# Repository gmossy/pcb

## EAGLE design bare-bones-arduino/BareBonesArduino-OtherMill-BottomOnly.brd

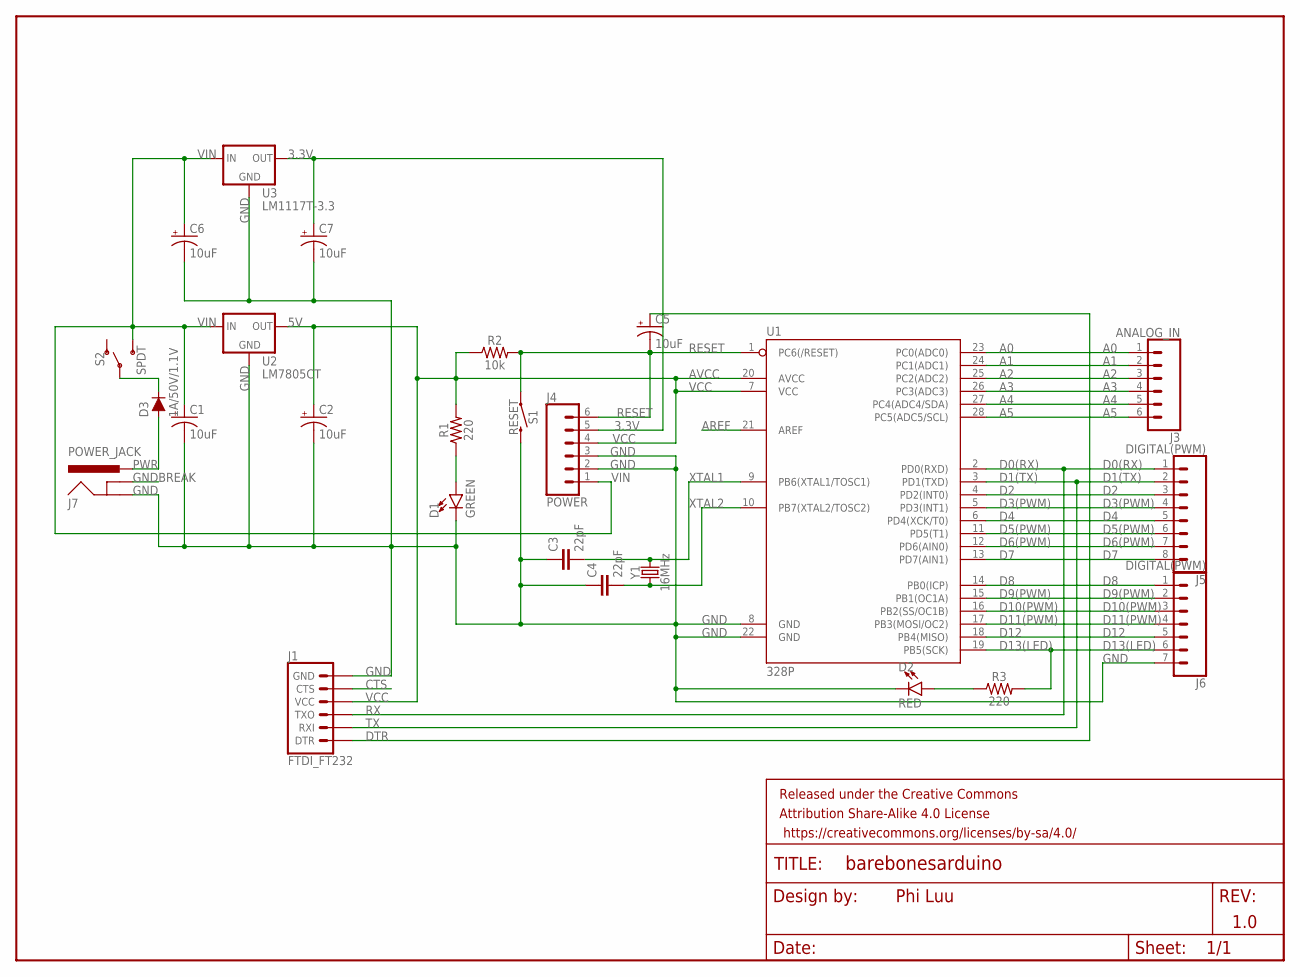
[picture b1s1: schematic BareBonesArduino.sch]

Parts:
C1, C2, C5, C6, C7: 10uF; CPOL-RADIAL-2.5MM-5MM
C3, C4: 22pF; CAP-PTH-2.54
D1: GREEN; LED_5MM
D2: RED; LED_5MM
D3: 1A/50V/1.1V; DIODE-1N4001
FRAME1: FRAME-LETTER; CREATIVE_COMMONS
J1: FTDI_FT232; 1X06
J3: ANALOG_IN; 1X06
J4: POWER; 1X06
J5: DIGITAL(PWM); 1X08
J6: DIGITAL(PWM); 1X07
J7: POWER_JACK; POWER_JACK_PTH
R1, R3: 220; AXIAL-0.3
R2: 10k; AXIAL-0.3
S1: RESET; TACTILE_SWITCH_PTH_6.0MM
S2: SPDT; SWITCH_SPDT_PTH_11.6X4.0MM
U1: 328P; DIP28
U2: LM7805CT; TO-220-ALT
U3: LM1117T-3.3; 78XXL
Y1: 16MHz; HC49US

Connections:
3.3V: C7.1 (+), J4.5, U3.GND (OUT)
A0: J3.1, U1.23 (PC0(ADC0))
A1: J3.2, U1.24 (PC1(ADC1))
A2: J3.3, U1.25 (PC2(ADC2))
A3: J3.4, U1.26 (PC3(ADC3))
A4: J3.5, U1.27 (PC4(ADC4/SDA))
A5: J3.6, U1.28 (PC5(ADC5/SCL))
AREF: U1.21 (AREF)
CTS: J1.5 (CTS)
D0(RX): J1.3 (TXO), J5.1, U1.2 (PD0(RXD))
D1(TX): J1.2 (RXI), J5.2, U1.3 (PD1(TXD))
D2: J5.3, U1.4 (PD2(INT0))
D3(PWM): J5.4, U1.5 (PD3(INT1))
D4: J5.5, U1.6 (PD4(XCK/T0))
D5(PWM): J5.6, U1.11 (PD5(T1))
D6(PWM): J5.7, U1.12 (PD6(AIN0))
D7: J5.8, U1.13 (PD7(AIN1))
D8: J6.1, U1.14 (PB0(ICP))
D9(PWM): J6.2, U1.15 (PB1(OC1A))
D10(PWM): J6.3, U1.16 (PB2(SS/OC1B))
D11(PWM): J6.4, U1.17 (PB3(MOSI/OC2))
D12: J6.5, U1.18 (PB4(MISO))
D13(LED): J6.6, R3.P$2 (2), U1.19 (PB5(SCK))
DTR: C5.1 (+), J1.1 (DTR)
GND: C1.2 (-), C2.2 (-), C3.1, C4.1, C6.2 (-), C7.2 (-), D1.K (C), D2.K (C), J1.6 (GND), J4.2, J4.3, J6.7, J7.GND, S1.3 (2), U1.8 (GND), U1.22 (GND), U2.GND, U3.IN (GND)
GNDBREAK: J7.GNDBREAK
unnamed: D2.A, R3.P$1 (1)
unnamed: D3.C, S2.2
unnamed: D1.A, R1.P$1 (1)
PWR: D3.A, J7.PWR
RESET: C5.2 (-), J4.6, R2.P$2 (2), S1.1, U1.1 (PC6(/RESET))
VCC: C2.1 (+), J1.4 (VCC), J4.4, R1.P$2 (2), R2.P$1 (1), U1.7 (VCC), U1.20 (AVCC), U2.OUT
VIN: C1.1 (+), C6.1 (+), J4.1, S2.3 (S), U2.IN, U3.OUT (IN)
XTAL1: C3.2, U1.9 (PB6(XTAL1/TOSC1)), Y1.2
XTAL2: C4.2, U1.10 (PB7(XTAL2/TOSC2)), Y1.1

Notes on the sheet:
Phi Luu
1.0
AVCC
GND

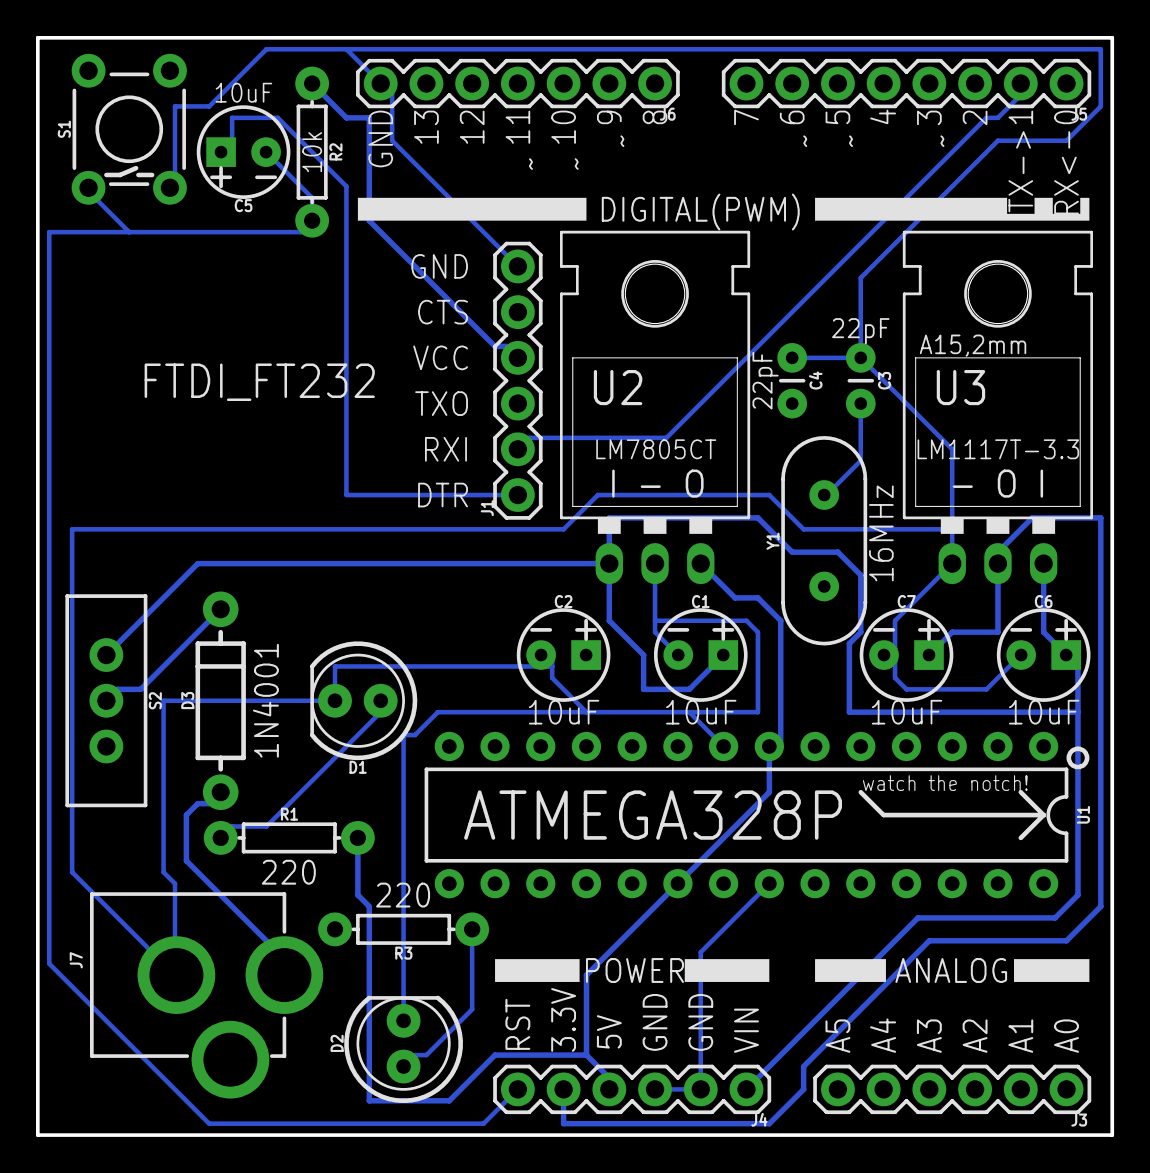
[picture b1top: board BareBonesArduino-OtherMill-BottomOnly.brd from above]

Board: 2 copper layers, 59.7 x 61.0 mm, 26 parts (0 on the bottom side), 32 nets.

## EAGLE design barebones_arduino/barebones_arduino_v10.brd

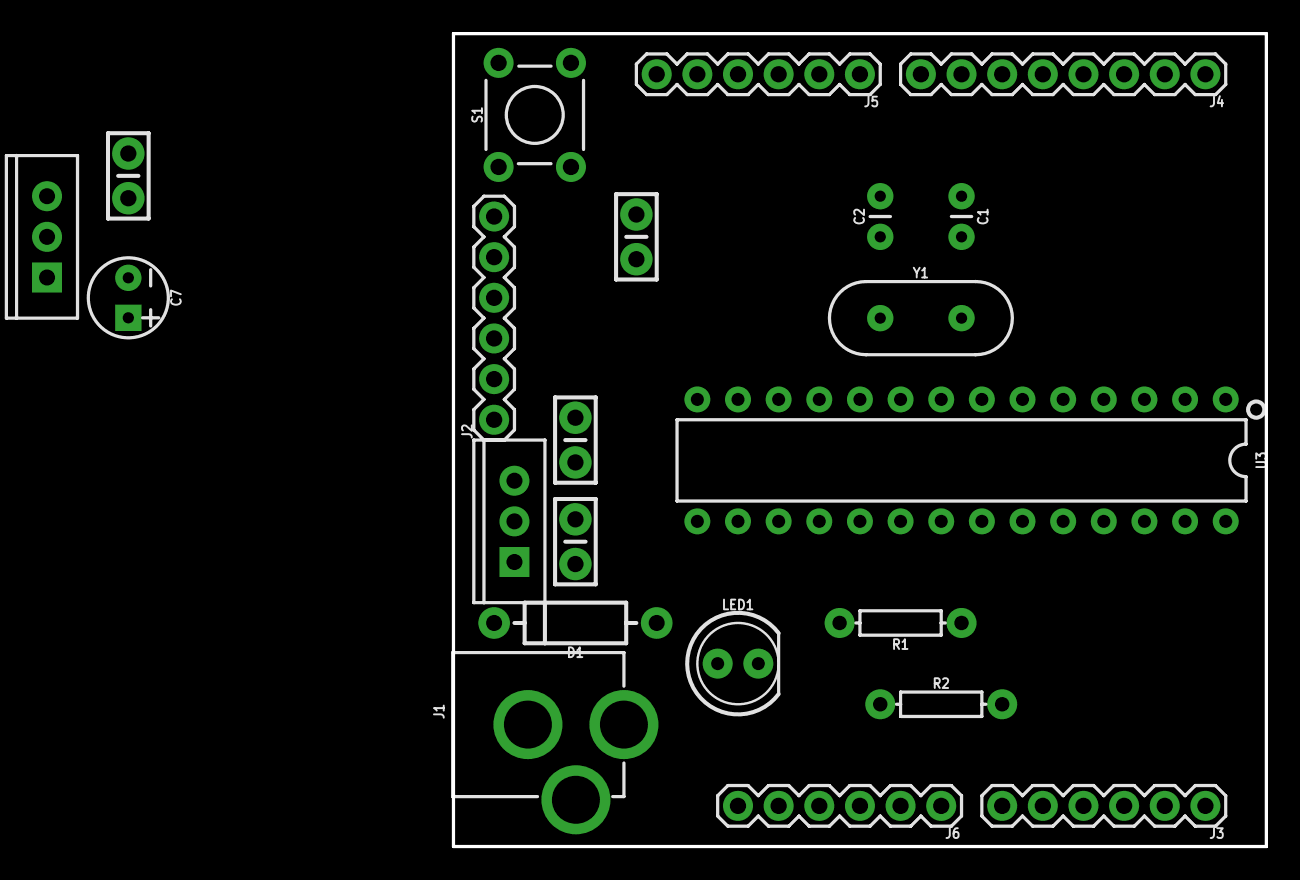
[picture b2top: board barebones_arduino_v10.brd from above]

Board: 2 copper layers, 50.8 x 50.8 mm, 23 parts (0 on the bottom side), 30 nets, no tracks yet.

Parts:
C1, C2: 22pF; CAP-PTH-2.54
C3: 1uF; CAP-PTH-SMALL-KIT
C4: 330nF; CAP-PTH-SMALL-KIT
C5: 0.1uF; CAP-PTH-SMALL-KIT
C6: 100nF; CAP-PTH-SMALL-KIT
C7: 10uF; CPOL-RADIAL-2.5MM-5MM
D1: 1N4001; DIODE-1N4001
FRAME1: FRAME-LETTER; CREATIVE_COMMONS
J1: POWER_JACK; POWER_JACK_PTH
J2: FTDI; 1X06
J3: ANALOG; 1X06
J4: DIGITAL; 1X08
J5: DIGITAL; 1X06
J6: POWER; 1X06
LED1: GREEN; LED_5MM
R1: 300; AXIAL-0.3
R2: 10k; AXIAL-0.3
S1: RESET; TACTILE_SWITCH_PTH_6.0MM
U1: LM7805; TO220-IGO
U2: LD1117-3.3; TO220-ADJ
U3: ATMEGA328P; DIP28
Y1: 16MHz; HC49US

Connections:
3.3V: C7.1, J6.5, U2.OUT
5V: C5.1, J2.4, J6.4, R1.P$1, R2.P$1, U1.OUT, U3.7
*D3: J4.4, U3.5
*D5: J4.6, U3.11
*D6: J4.7, U3.12
*D9: J5.2, U3.15
*D10: J5.3, U3.16
*D11: J5.4, U3.17
A0: J3.1, U3.23
A1: J3.2, U3.24
A2: J3.3, U3.25
A3: J3.4, U3.26
A4: J3.5, U3.27
A5: J3.6, U3.28
D0(RX): J2.3, J4.1, U3.2
D1(TX): J2.2, J4.2, U3.3
D2: J4.3, U3.4
D4: J4.5, U3.6
D7: J4.8, U3.13
D8: J5.1, U3.14
D12: J5.5, U3.18
D13: J5.6, U3.19
DTR: C3.1, J2.1
GND: C1.1, C2.2, C4.2, C5.2, C6.2, C7.2, J1.GND, J1.GNDBREAK, J2.6, J6.2, J6.3, LED1.K, S1.3, U1.GND, U2.ADJ, U3.8, U3.22
unnamed: D1.A, J1.PWR
POWER_LED: LED1.A, R1.P$2
RAW: C4.1, C6.1, D1.C, J6.1, U1.IN, U2.IN
RESET: C3.2, J6.6, R2.P$2, S1.1, U3.1
XTAL1: C1.2, U3.9, Y1.2
XTAL2: C2.1, U3.10, Y1.1

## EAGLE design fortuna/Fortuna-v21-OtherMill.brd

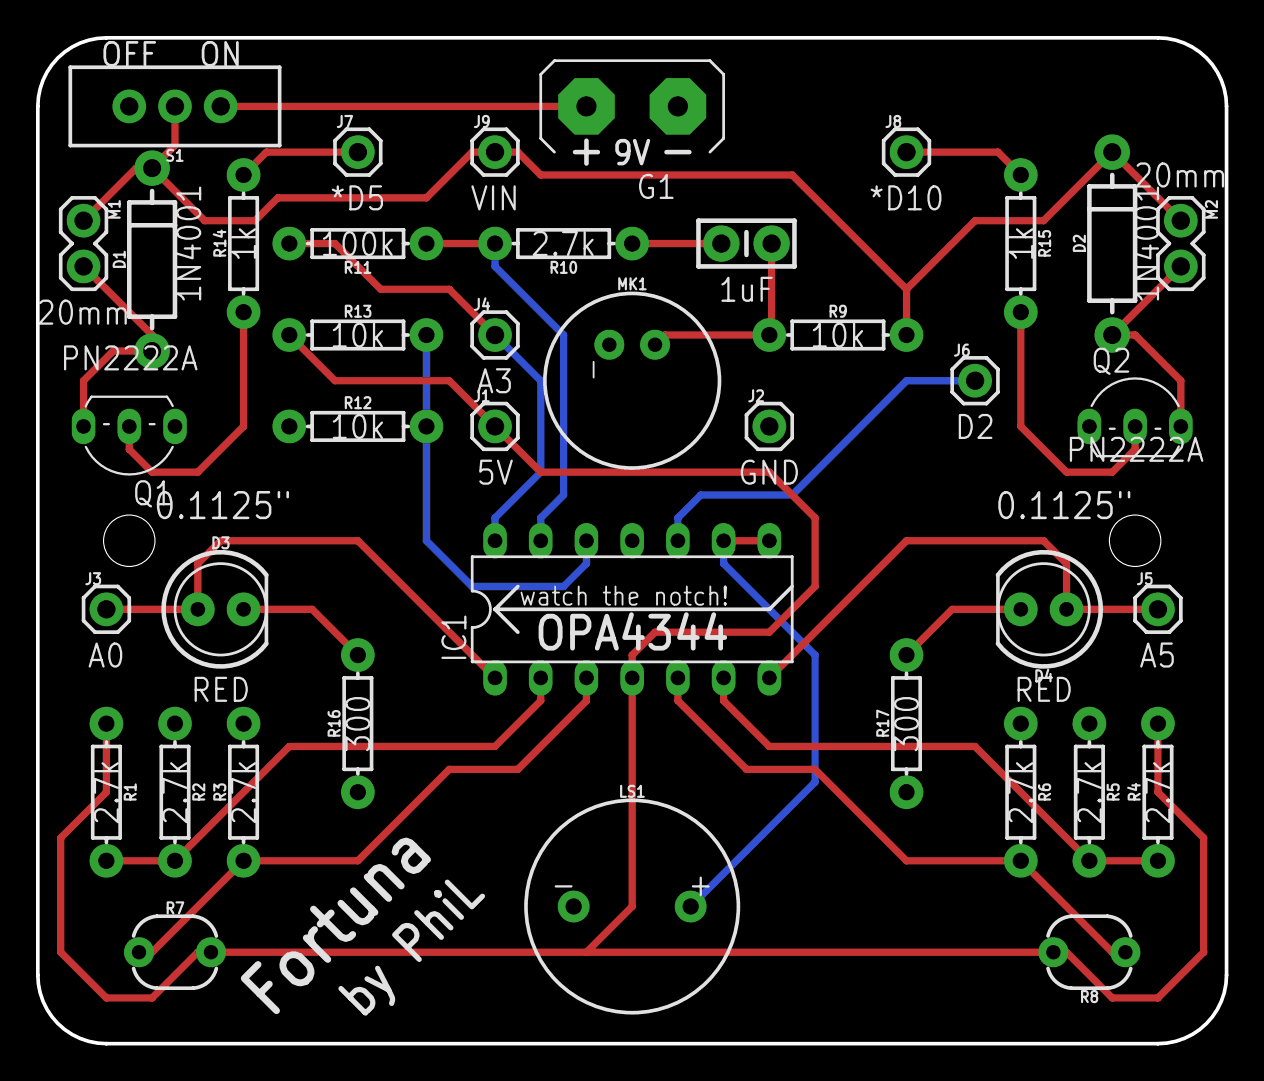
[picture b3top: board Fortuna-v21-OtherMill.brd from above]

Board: 2 copper layers, 66.0 x 55.9 mm, 41 parts (0 on the bottom side), 25 nets.

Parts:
C1: 1uF; CAP-PTH-SMALL-KIT
D1, D2: 1N4001; DIODE-1N4001
D3: LLED_RED; LED_5MM
D4: RLED_RED; LED_5MM
FRAME1: FRAME-LETTER; CREATIVE_COMMONS
G1: AB9V
IC1: OPA4340P; DIL14
J1: 5V; 1X01
J2: GND; 1X01
J3: A0; 1X01
J4: A3; 1X01
J5: A5; 1X01
J6: D2; 1X01
J7: *D5; 1X01
J8: *D10; 1X01
J9: VIN; 1X01
LS1: BUZZER; BUZZER-12MM
M1, M2: MOTOR20MM; 1X02
MK1: MIC; MICROPHONE-PTH-9.7MM
Q1, Q2: PN2222A; TO92-EBC-OVAL
R1, R2, R3, R4, R5, R6, R10: 2.7k; AXIAL-0.3
R7: LPHOTO; PHOTOCELL
R8: RPHOTO; PHOTOCELL
R9, R12, R13: 10k; AXIAL-0.3
R11: 100k; AXIAL-0.3
R14, R15: 1k; AXIAL-0.3
R16, R17: 300; AXIAL-0.3
S1: ON/OFF; SWITCH_SPDT_PTH_11.6X4.0MM

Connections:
5V: IC1.4, J1.1, R1.P$1, R4.P$2, R7.2, R8.2, R13.P$1
9V: G1.+, S1.3
+BUZZER: IC1.10, J6.1
+LPHOTO: IC1.3, R3.P$1, R7.1
+MIC: IC1.12, R12.P$2, R13.P$2
+RPHOTO: IC1.5, R6.P$2, R8.1
-LPHOTO: IC1.2, R1.P$2, R2.P$2
-MIC: IC1.13, R10.P$2, R11.P$1
-RPHOTO: IC1.6, R4.P$1, R5.P$2
GND: G1.-, IC1.11, J2.1, LS1.-, MK1.GND, Q1.E, Q2.E, R2.P$1, R3.P$2, R5.P$1, R6.P$1, R12.P$1, R16.P$1, R17.P$1
unnamed: C1.2, MK1.OUT, R9.P$1
unnamed: C1.1, R10.P$1
unnamed: D3.K, R16.P$2
unnamed: D4.K, R17.P$2
unnamed: Q1.B, R14.P$1
unnamed: D1.A, M1.2, Q1.C
unnamed: D2.A, M2.2, Q2.C
unnamed: Q2.B, R15.P$2
OUT_BUZZER: IC1.8, IC1.9, LS1.+
OUT_LMOTOR: J7.1, R14.P$2
OUT_LPHOTO: D3.A, IC1.1, J3.1
OUT_MIC: IC1.14, J4.1, R11.P$2
OUT_RMOTOR: J8.1, R15.P$1
OUT_RPHOTO: D4.A, IC1.7, J5.1
VCC: D1.C, D2.C, J9.1, M1.1, M2.1, R9.P$2, S1.2

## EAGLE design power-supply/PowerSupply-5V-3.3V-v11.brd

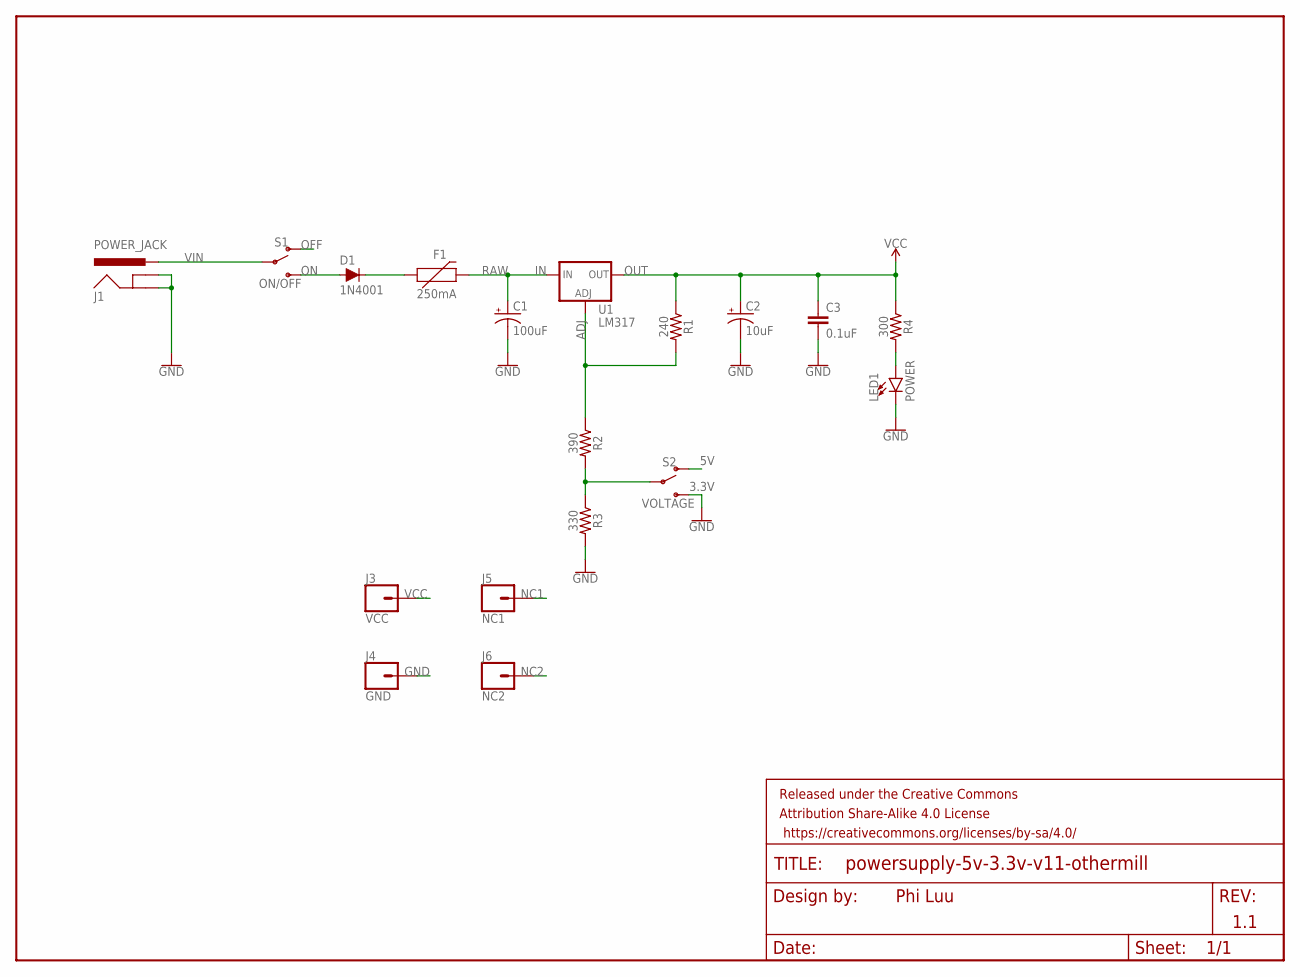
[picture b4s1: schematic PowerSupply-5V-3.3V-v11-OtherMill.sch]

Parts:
C1: 100uF; CPOL-RADIAL-2.5MM-6.5MM
C2: 10uF; CPOL-RADIAL-2.5MM-5MM
C3: 0.1uF; CAP-PTH-SMALL-KIT
D1: 1N4001; DIODE-1N4001
F1: 250mA; PTH
FRAME1: FRAME-LETTER; CREATIVE_COMMONS
J1: POWER_JACK; POWER_JACK_PTH
J3: VCC; 1X01
J4: GND; 1X01
J5: NC1; 1X01
J6: NC2; 1X01
LED1: POWER; LED_5MM
R1: 240; AXIAL-0.3
R2: 390; AXIAL-0.3
R3: 330; AXIAL-0.3
R4: 300; AXIAL-0.3
S1: ON/OFF; SWITCH_SPDT_PTH_11.6X4.0MM
S2: VOLTAGE; SWITCH_SPDT_PTH_11.6X4.0MM
U1: LM317; TO220-ADJ

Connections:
5V: S2.1 (O)
ADJ: R1.P$2 (2), R2.P$1 (1), U1.ADJ
GND: C1.2 (-), C2.2 (-), C3.2, J1.GND, J1.GNDBREAK, J4.1, LED1.K (C), R3.P$2 (2), S2.3 (S)
LED: LED1.A, R4.P$2 (2)
unnamed: D1.C, F1.P$1 (1)
unnamed: R2.P$2 (2), R3.P$1 (1), S2.2
NC1: J5.1
NC2: J6.1
OFF: S1.1 (O)
ON: D1.A, S1.3 (S)
RAW: C1.1 (+), F1.P$2 (2), U1.IN
VCC: C2.1 (+), C3.1, J3.1, R1.P$1 (1), R4.P$1 (1), U1.OUT
VIN: J1.PWR, S1.2

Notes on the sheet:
Phi Luu
1.1
OUT
3.3V

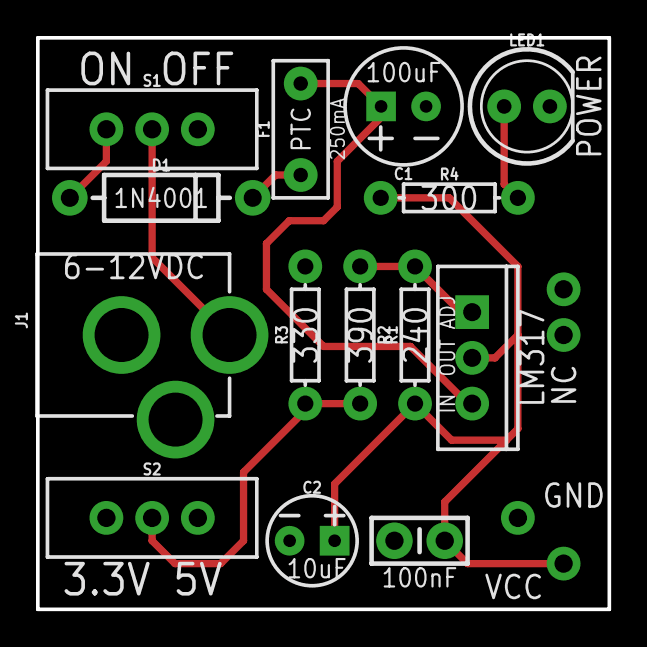
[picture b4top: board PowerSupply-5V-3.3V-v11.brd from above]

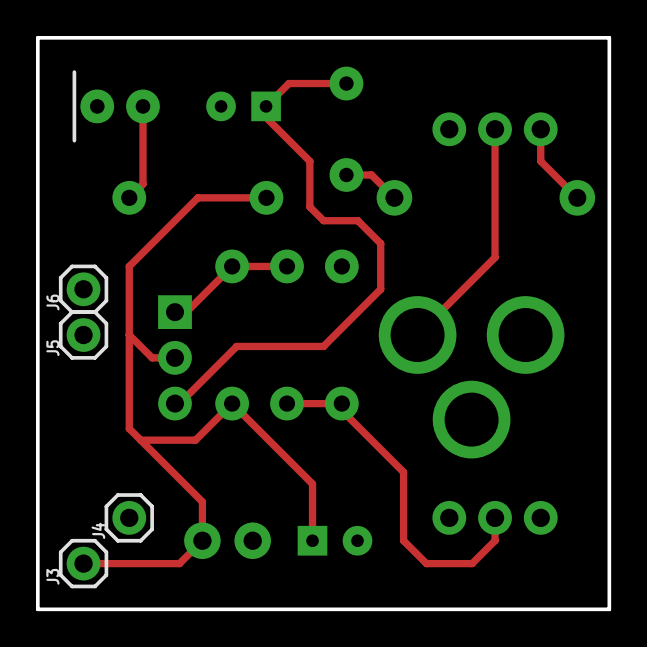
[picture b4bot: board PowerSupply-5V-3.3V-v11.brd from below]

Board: 2 copper layers, 31.8 x 31.8 mm, 19 parts (4 on the bottom side), 9 nets.

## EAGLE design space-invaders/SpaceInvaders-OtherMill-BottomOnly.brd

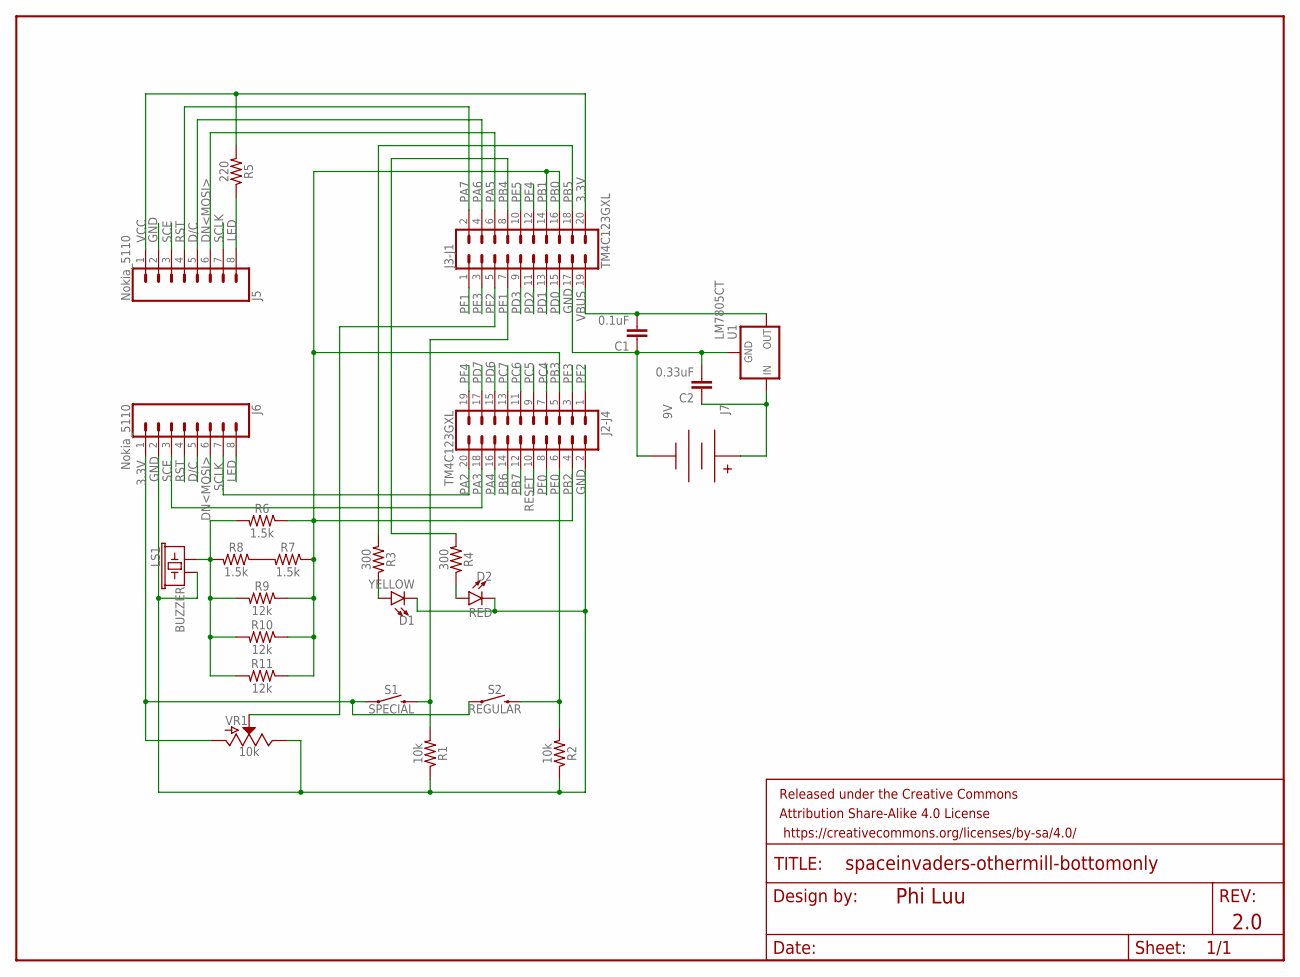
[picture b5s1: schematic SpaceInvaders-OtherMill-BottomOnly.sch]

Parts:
C1: 0.1uF; CAP-PTH-SMALL-KIT
C2: 0.33uF; CAP-PTH-SMALL-KIT
D1: YELLOW; LED_5MM
D2: RED; LED_5MM
FRAME1: FRAME-LETTER; CREATIVE_COMMONS
J2-J4, J3-J1: TM4C123GXL; 2X10
J5, J6: Nokia_5110; 1X08
J7: 9V; BC9VPC
LS1: BUZZER; BUZZER-12MM
R1, R2: 10k; AXIAL-0.3
R3, R4: 300; AXIAL-0.3
R5: 220; AXIAL-0.3
R6, R7, R8: 1.5k; AXIAL-0.3
R9, R10, R11: 12k; AXIAL-0.3
S1: SPECIAL; TACTILE_SWITCH_PTH_6.0MM
S2: REGULAR; TACTILE_SWITCH_PTH_6.0MM
U1: LM7805CT; TO-220-ALT
VR1: 10k; SLIDER-MEDIUM

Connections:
3.3V: J3-J1.20, J5.1, J6.1, R5.P$2 (2), S1.1, S2.1, VR1.BOTTOM (A)
9V: C2.1, J7.V+, U1.IN
D/C: J6.5
DAC_OUT: LS1.+ (1), R6.P$2 (2), R8.P$2 (2), R9.P$2 (2), R10.P$2 (2), R11.P$2 (2)
DN<MOSI>: J6.6
GND: C1.1, C2.2, D1.K (C), D2.K (C), J2-J4.2, J3-J1.17, J5.2, J6.2, J7.V-, LS1.- (2), R1.P$1 (1), R2.P$1 (1), U1.GND, VR1.TOP (E)
LED: J5.8, J6.8, R5.P$1 (1)
LLED: D1.A, R3.P$1 (1)
unnamed: R7.P$2 (2), R8.P$1 (1)
PA2: J2-J4.20, J6.7
PA3: J2-J4.18, J6.3
PA4: J2-J4.16
PA5: J3-J1.6, J5.6
PA6: J3-J1.4, J5.5
PA7: J3-J1.2, J5.4
PB2: J2-J4.4, J2-J4.5, J3-J1.14, J3-J1.16, R6.P$1 (1), R7.P$1 (1), R9.P$1 (1), R10.P$1 (1), R11.P$1 (1)
PB4: J3-J1.8, R4.P$2 (2)
PB5: J3-J1.18, R3.P$2 (2)
PB6: J2-J4.14
PB7: J2-J4.12
PC4: J2-J4.7
PC5: J2-J4.9
PC6: J2-J4.11
PC7: J2-J4.13
PD0: J3-J1.15
PD1: J3-J1.13
PD2: J3-J1.11
PD3: J3-J1.9
PD6: J2-J4.15
PD7: J2-J4.17
PE0: J2-J4.6, R2.P$2 (2), S2.3 (2)
PE1: J3-J1.7, R1.P$2 (2), S1.3 (2)
PE2: J3-J1.5, VR1.WIPER (S)
PE3: J3-J1.3
PE4: J3-J1.12
PE5: J3-J1.10
PF0: J2-J4.8
PF1: J3-J1.1
PF2: J2-J4.1
PF3: J2-J4.3
PF4: J2-J4.19
RESET: J2-J4.10
RLED: D2.A, R4.P$1 (1)
RST: J6.4
SCE: J5.3
SCLK: J5.7
VBUS: C1.2, J3-J1.19, U1.OUT

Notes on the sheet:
Phi Luu
2.0
PB0
PB1
PB3
VCC
RST
D/C
DN<MOSI>
SCE
SCLK

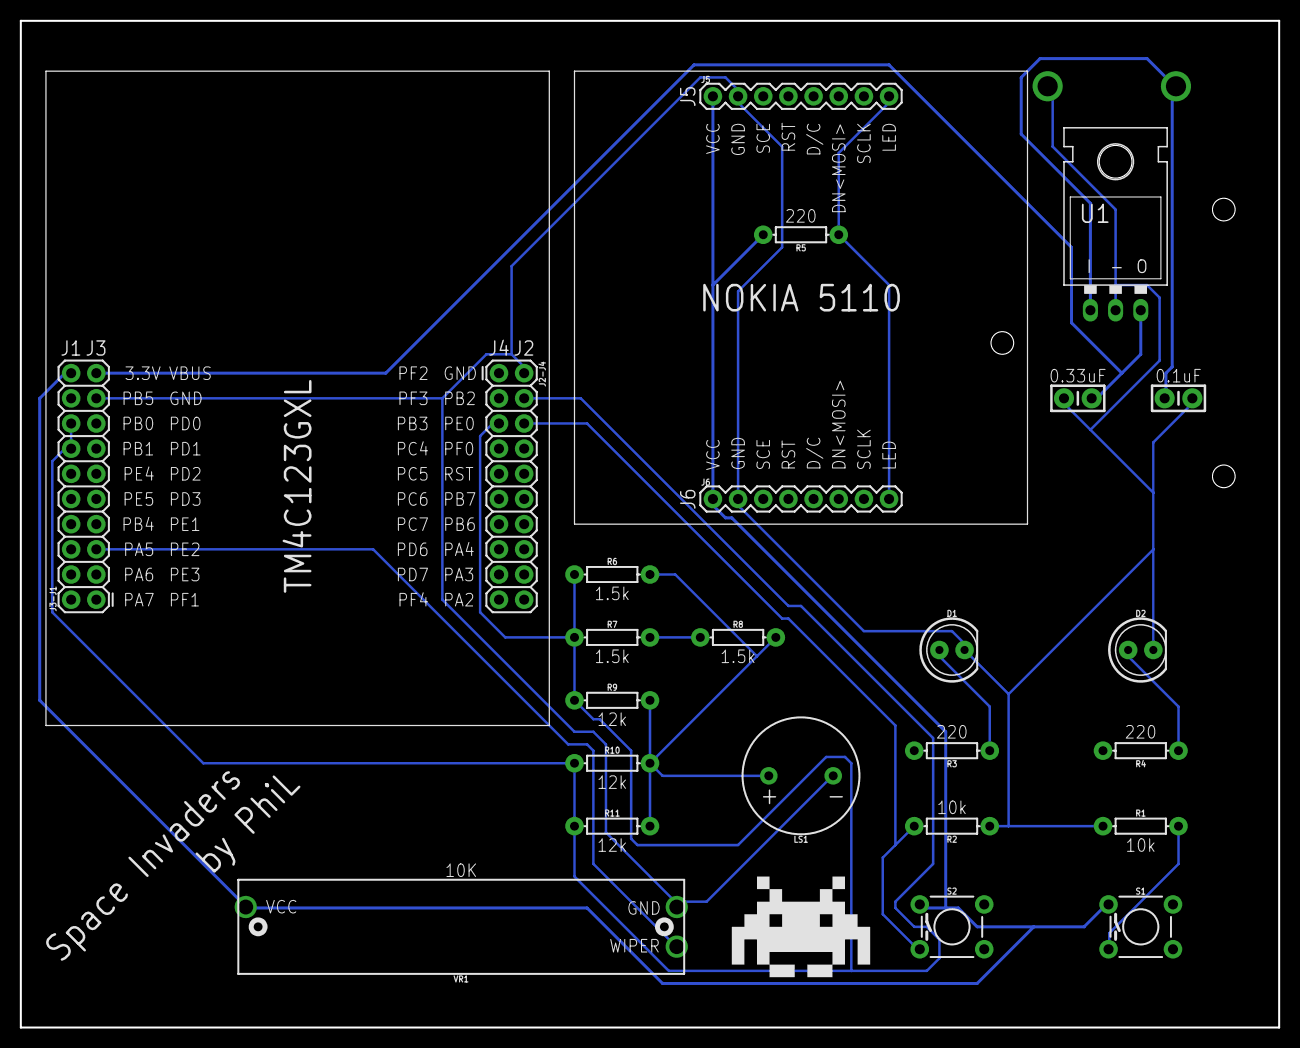
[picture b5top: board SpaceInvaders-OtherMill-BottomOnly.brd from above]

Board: 2 copper layers, 127.0 x 101.6 mm, 26 parts (1 on the bottom side), 20 nets.

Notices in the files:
parts and their libraries:
SparkFun-Capacitors: Licensing: Creative Commons ShareAlike 4.0 International - https://creativecommons.org/licenses/by-sa/4.0
SparkFun-Aesthetics: Released under the Creative Commons Attribution Share-Alike 4.0 License
SparkFun-Aesthetics: https://creativecommons.org/licenses/by-sa/4.0
